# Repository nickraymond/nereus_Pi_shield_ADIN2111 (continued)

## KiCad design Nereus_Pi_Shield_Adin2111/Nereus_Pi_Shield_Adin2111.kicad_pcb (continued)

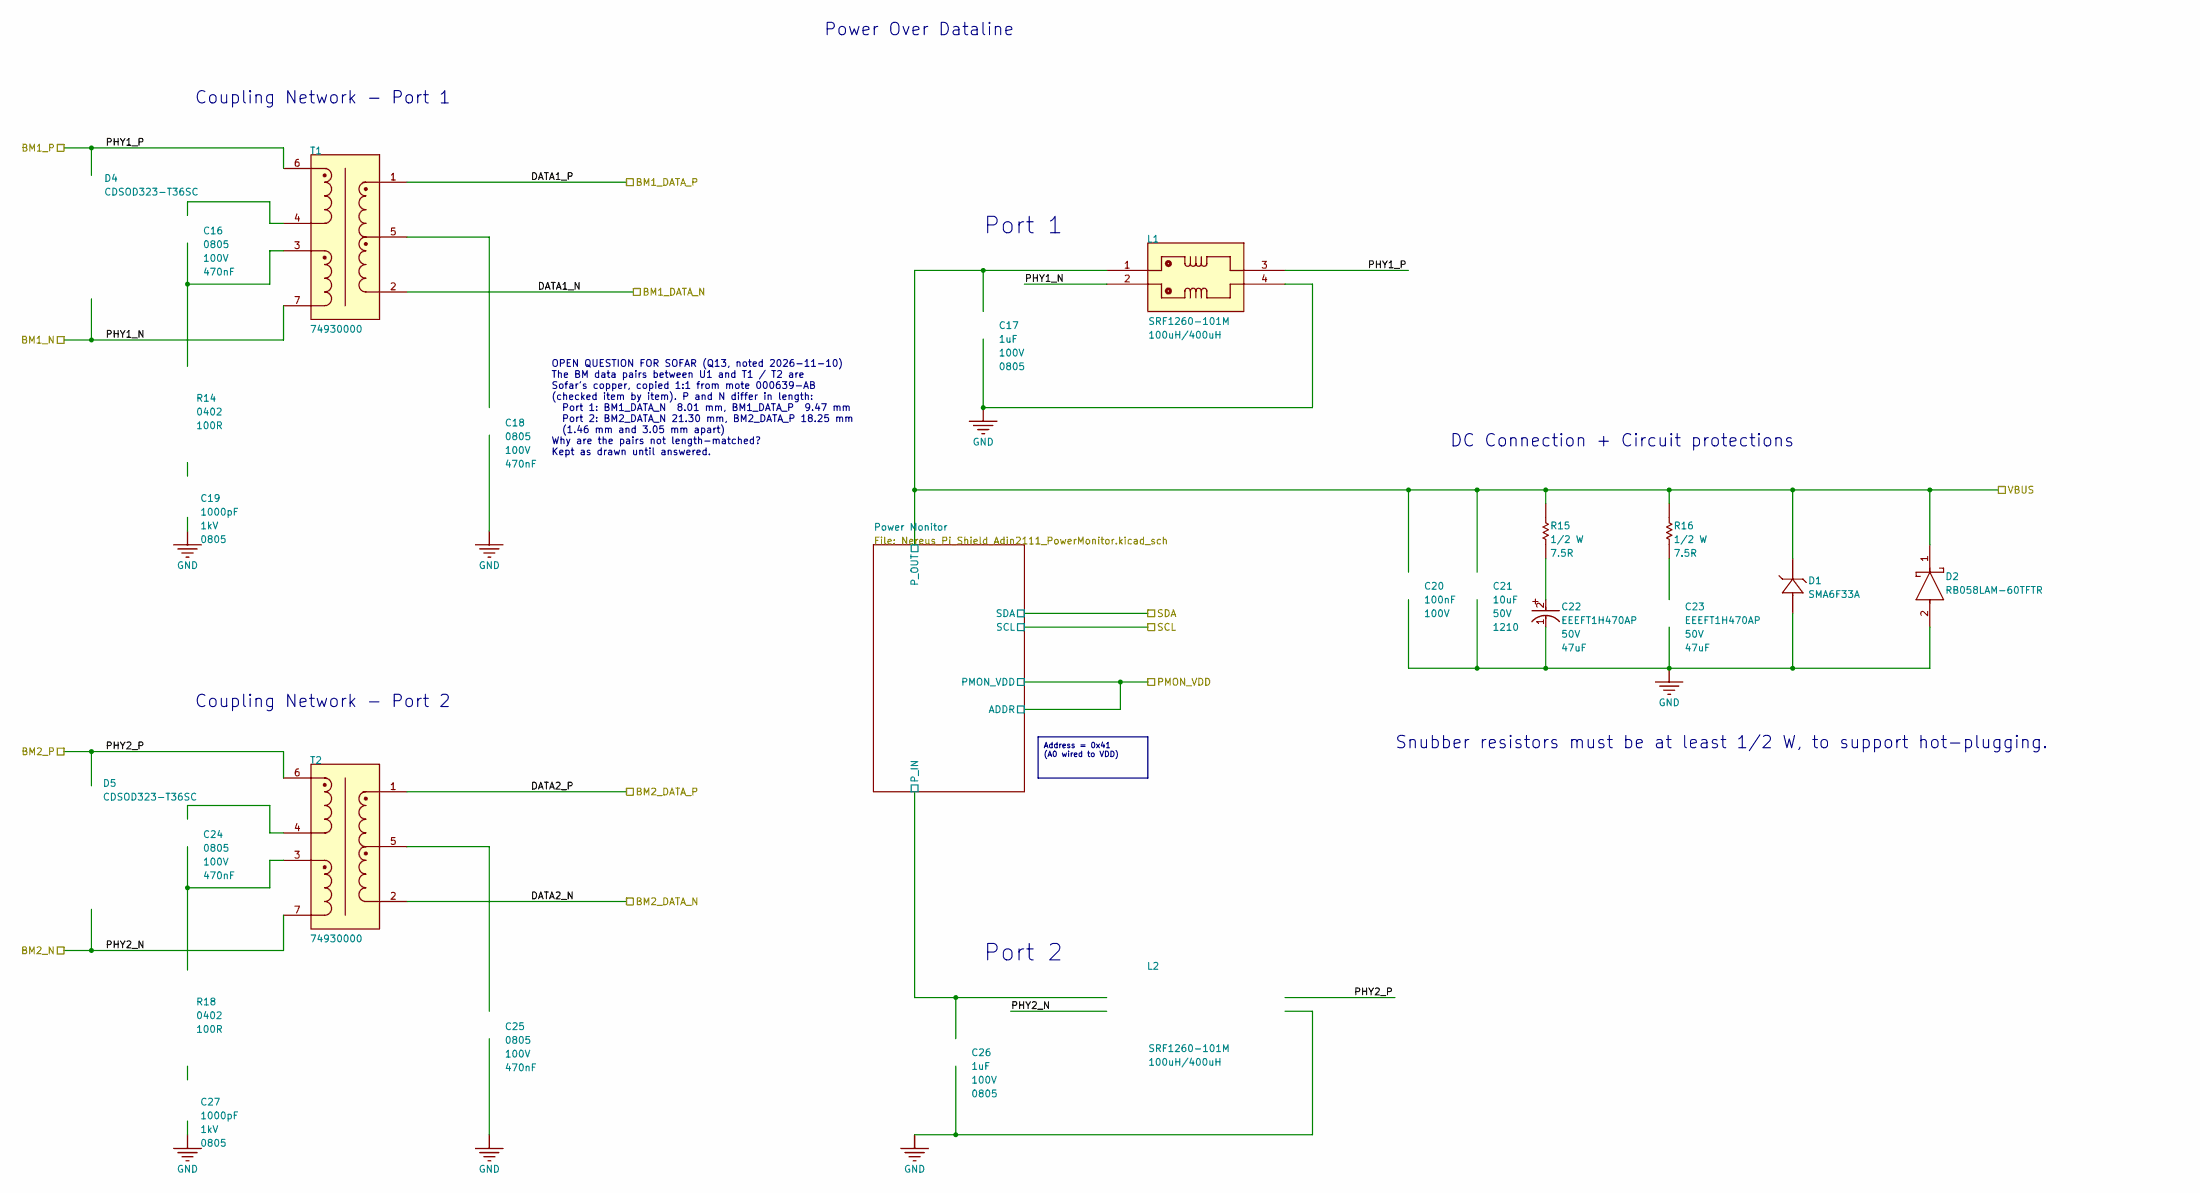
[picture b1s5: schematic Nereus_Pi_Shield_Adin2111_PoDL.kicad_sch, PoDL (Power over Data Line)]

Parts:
C16, C18, C24, C25: 08051C474KAT2A; FP-0805-L_2_01_0_2-W_1_25-MFG; TOLERANCE 10%; VOLTAGE RATING 100V
C17, C26: C2012X7S2A105K125AB; FP-C2012-125-0_2-MFG; VOLTAGE RATING (DC) 100V; VOLTAGE 100V
C19, C27: C0805C102MDRACTU; CAPC2013X145X50LL20T25; VOLTAGE 1kV; PART NUMBER C0805C102MDRACTU
C20: GRM188R72A104KA35D; FP-GRM188-0_1-e0_2_0_5-IPC_B; VOLTAGE RATING (DC) 100V; VOLTAGE 100V
C21: CL32B106KBJNNNE; FP-CL32-IPC_C; VOLTAGE RATING (DC) 50V; VOLTAGE RATING 50V
C22, C23: EEEFT1H470AP; FP-FTD-MFG; VOLTAGE 50V; TOLERANCE 20%
D1: SMA6F33A; SMA6F33A-Footprint-1; VOLTAGE - CLAMPING (MAX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 53.1V; VOLTAGE - REVERSE STAND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 33V; MANUFACTURERPARTNUMBER1 SMA6F33A-M3/H
D2: RB058LAM-60TFTR; FP-PMDTM-MFG
D4, D5: CDSOD323-T36SC; FP-SOD-323-MFG; BREAKDOWN VOLTAGE 40V; CLAMPING VOLTAGE 75V; MANUFACTURER PART NUMBER CDSOD323-T36SC; DIGIKEY DESCRIPTION TVS DIODE 36V 75V SOD323
L1, L2: SRF1260-101M; SRF1260-101M-Footprint-1
R14, R18: RR0510P-101-D; FP-RR0510-IPC_B; RESISTANCE TOLERANCE 0.5%; POWER RATING 63mW
R15, R16: CRCW08057R50FKEAHP; CRCW08057R50FKEAHP-Footprint-1; MANUFACTURERPARTNUMBER CRCW08057R50FKEAHP
T1, T2: 74930000; FP-74930000-MFG

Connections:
/Top-Level Schematic/BM1_DATA_N: T1.2; also elsewhere on the board
/Top-Level Schematic/BM1_DATA_P: T1.1; also elsewhere on the board
/Top-Level Schematic/BM1_N: D4.2, L1.2, T1.7; also elsewhere on the board
/Top-Level Schematic/BM1_P: D4.1, L1.3, T1.6; also elsewhere on the board
/Top-Level Schematic/BM2_DATA_N: T2.2; also elsewhere on the board
/Top-Level Schematic/BM2_DATA_P: T2.1; also elsewhere on the board
/Top-Level Schematic/BM2_N: D5.2, L2.2, T2.7; also elsewhere on the board
/Top-Level Schematic/BM2_P: D5.1, L2.3, T2.6; also elsewhere on the board
/Top-Level Schematic/PoDL/Power Monitor/P_IN: C26.1, L2.1; also elsewhere on the board
GND: C17.2, C18.1, C19.1, C20.2, C21.2, C22.1 (C), C23.1 (C), C25.1, C26.2, C27.1, D1.1 (ANODE), D2.2 (A), L1.4, L2.4; also elsewhere on the board
unnamed: C16.1, R14.1, T1.3
unnamed: C16.2, T1.4
unnamed: C18.2, T1.5
unnamed: C19.2, R14.2
unnamed: C22.2 (A), R15.1
unnamed: C23.2 (A), R16.1
unnamed: C24.1, R18.1, T2.3
unnamed: C24.2, T2.4
unnamed: C25.2, T2.5
unnamed: C27.2, R18.2
VBUS: C17.1, C20.1, C21.1, D1.2 (CATHODE), D2.1 (C), L1.1, R15.2, R16.2; also elsewhere on the board

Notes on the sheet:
OPEN QUESTION FOR SOFAR (Q13, noted 2026-11-10) The BM data pairs between U1 and T1 / T2 are Sofar's copper, copied 1:1 from mote 000639-AB (checked item by item). P and N differ in length: Port 1: BM1_DATA_N 8.01 mm, BM1_DATA_P 9.47 mm Port 2: BM2_DATA_N 21.30 mm, BM2_DATA_P 18.25 mm (1.46 mm and 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
Coupling Network - Port 2
DC Connection + Circuit protections
Snubber resistors must be at least 1/2 W, to support hot-plugging.
Port 2
Coupling Network - Port 1
Port 1
Address = 0x41 (A0 wired to VDD)
Power Over Dataline

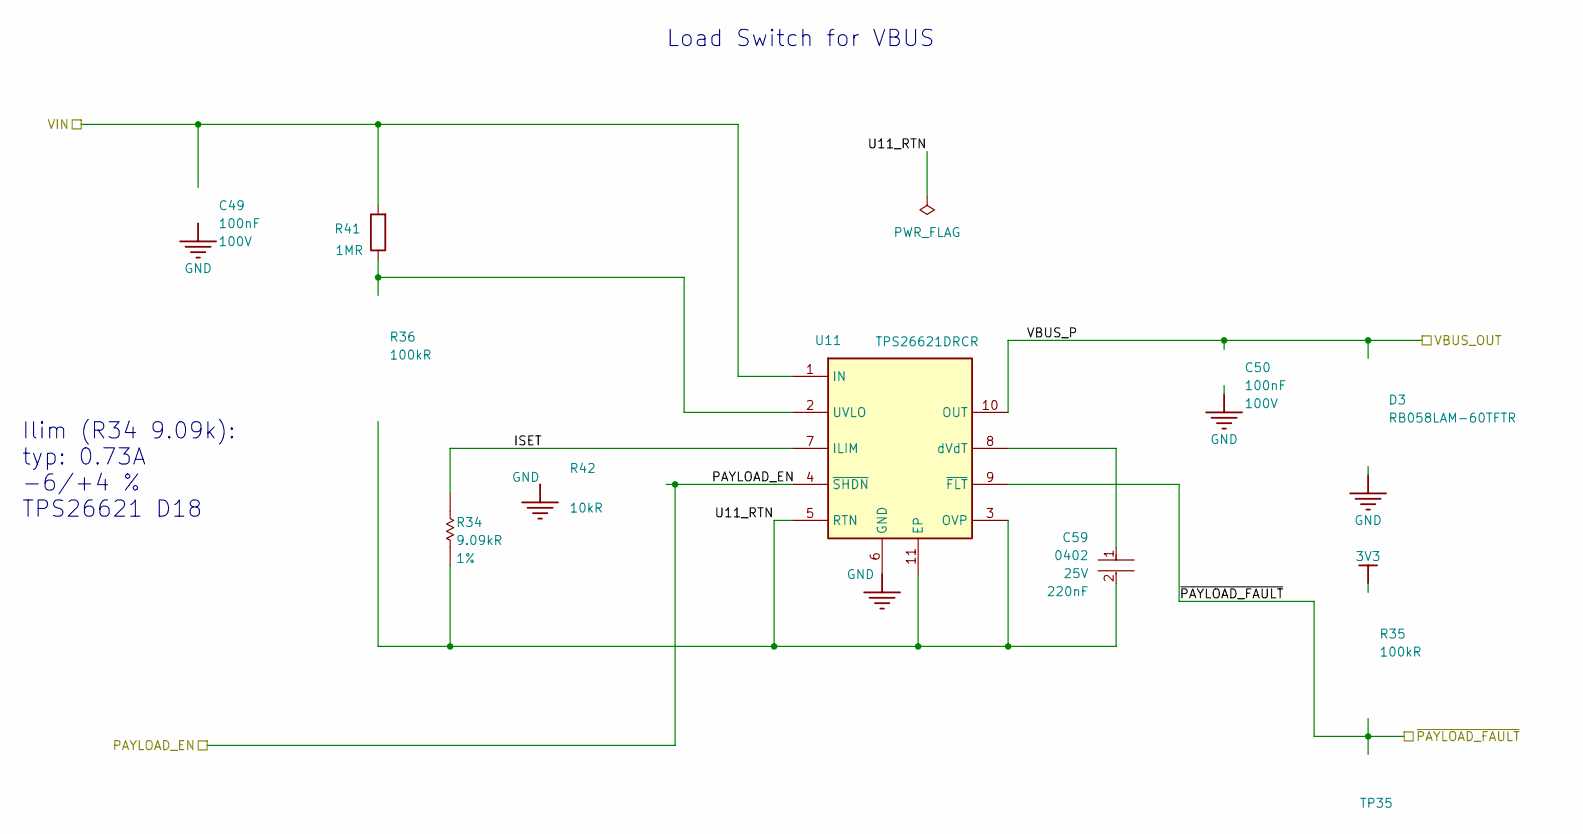
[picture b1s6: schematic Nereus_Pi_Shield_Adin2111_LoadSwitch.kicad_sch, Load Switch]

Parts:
C49, C50: GRM188R72A104KA35D; FP-GRM188-0_1-e0_2_0_5-IPC_B; VOLTAGE RATING (DC) 100V; VOLTAGE 100V
C59: CL05A224KA5NNNC; FP-CL278-IPC_C; VOLTAGE 25V; VOLTAGE RATING 25V
D3: RB058LAM-60TFTR; FP-PMDTM-MFG
R34: RC0402FR-079K09L; FP-RC0402-0_4-IPC_C; TOLERANCE 1%; PART NUMBER RC0402FR-079K09L
R35, R36: RMCF0402FT100K; FP-RMCF0402-IPC_C; TOLERANCE 1%; POWER RATING 62.5mW
R41: RC0402FR-071ML; R_0402_1005Metric; PART NUMBER RC0402FR-071ML
R42: RMCF0402FT10K0; FP-RMCF0402-IPC_C; TOLERANCE 1%; POWER RATING 62.5mW
TP35: TEST_POINT; PCB_TP_1.5mm; PARTTYPE non BOM
U11: TPS26621DRCR; Texas_DRC0010J; LCSC C1848341

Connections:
3V3: R35.2; also elsewhere on the board
/Top-Level Schematic/Load Switch/ISET: R34.2, U11.7 (ILIM)
/Top-Level Schematic/Load Switch/U11_RTN: C59.2, R34.1, R36.1, U11.3 (OVP), U11.5 (RTN), U11.11 (EP)
/Top-Level Schematic/PAYLOAD_EN: R42.1, U11.4 (~SHDN); also elsewhere on the board
/Top-Level Schematic/~PAYLOAD_FAULT: R35.1, TP35.1 (1_1), U11.9 (~FLT); also elsewhere on the board
GND: C49.2, C50.2, D3.2 (A), R42.2, U11.6 (GND); also elsewhere on the board
unnamed: R36.2, R41.1, U11.2 (UVLO)
unnamed: C59.1, U11.8 (dVdT)
VBUS: C49.1, R41.2, U11.1 (IN); also elsewhere on the board
VBUS_OUT: C50.1, D3.1 (C), U11.10 (OUT); also elsewhere on the board

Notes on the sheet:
Load Switch for VBUS
Ilim (R34 9.09k): typ: 0.73A -6/+4 % TPS26621 D18

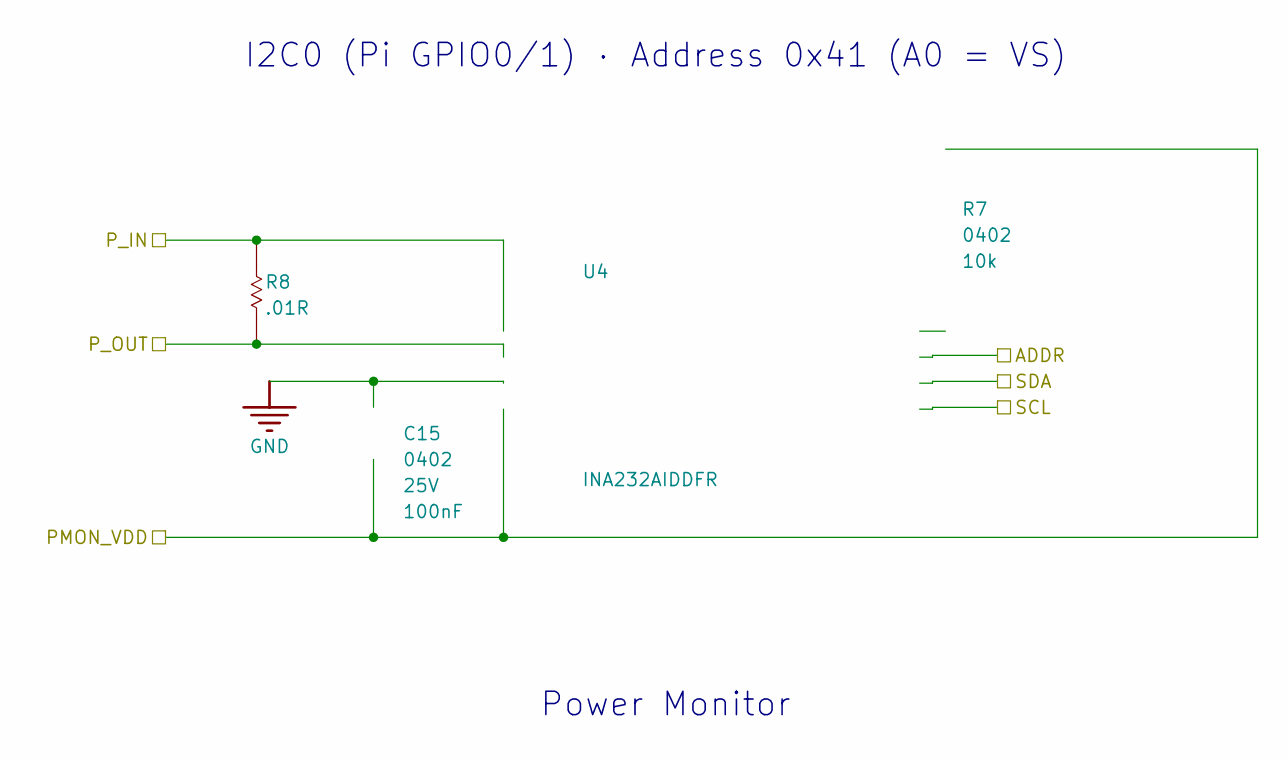
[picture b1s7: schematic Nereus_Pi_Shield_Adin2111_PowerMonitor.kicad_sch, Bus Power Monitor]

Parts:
C15: CL05A104KA5NNNC; FP-CL278-IPC_C; VOLTAGE 25V; VOLTAGE RATING 25V
R7: RC0402JR-0710KL; FP-RC0402-0_4-IPC_C; RESISTANCE TOLERANCE 5%; POWER RATING 62.5mW
R8: UR73D1JTTD10L0F; RESC1608X60X55ML20T10; MANUFACTURERPARTNUMBER UR73D1JTTD10L0F
U4: INA232AIDDFR; INA232AIDDFR-Footprint-1

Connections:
3V3: C15.2, R7.1, U4.4 (VS), U4.7 (A0); also elsewhere on the board
/Top-Level Schematic/I2C0_SCL: U4.5 (SCL); also elsewhere on the board
/Top-Level Schematic/I2C0_SDA: U4.6 (SDA); also elsewhere on the board
/Top-Level Schematic/PoDL/Power Monitor/P_IN: R8.2, U4.1 (IN+); also elsewhere on the board
GND: C15.1, U4.3 (GND); also elsewhere on the board
unnamed: R7.2, U4.8 (ALERT)
VBUS: R8.1, U4.2 (IN-); also elsewhere on the board

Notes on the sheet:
I2C0 (Pi GPIO0/1) · Address 0x41 (A0 = VS)
Power Monitor

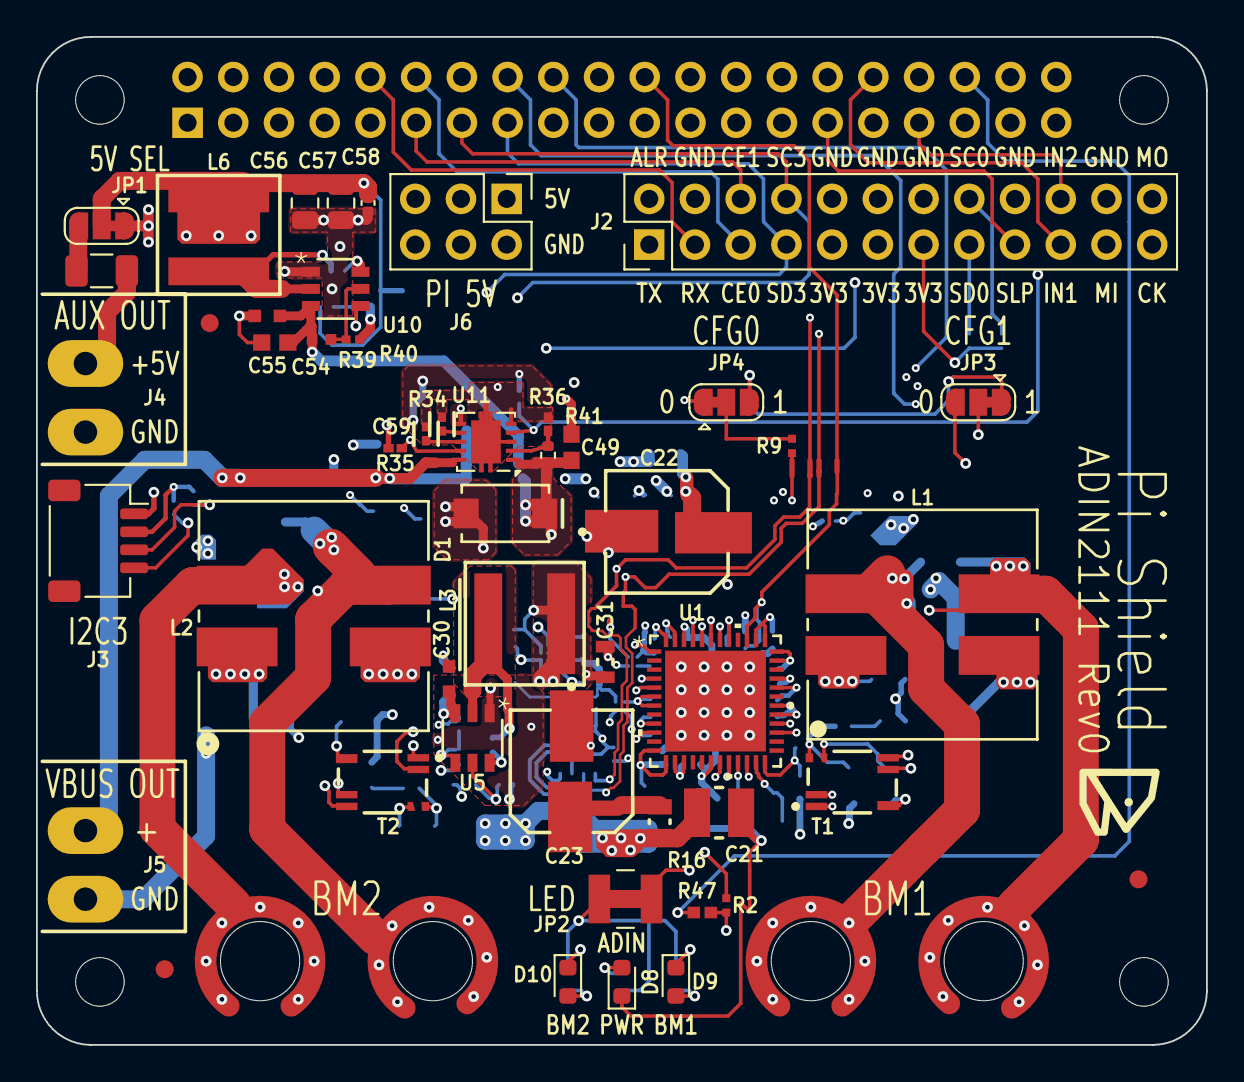
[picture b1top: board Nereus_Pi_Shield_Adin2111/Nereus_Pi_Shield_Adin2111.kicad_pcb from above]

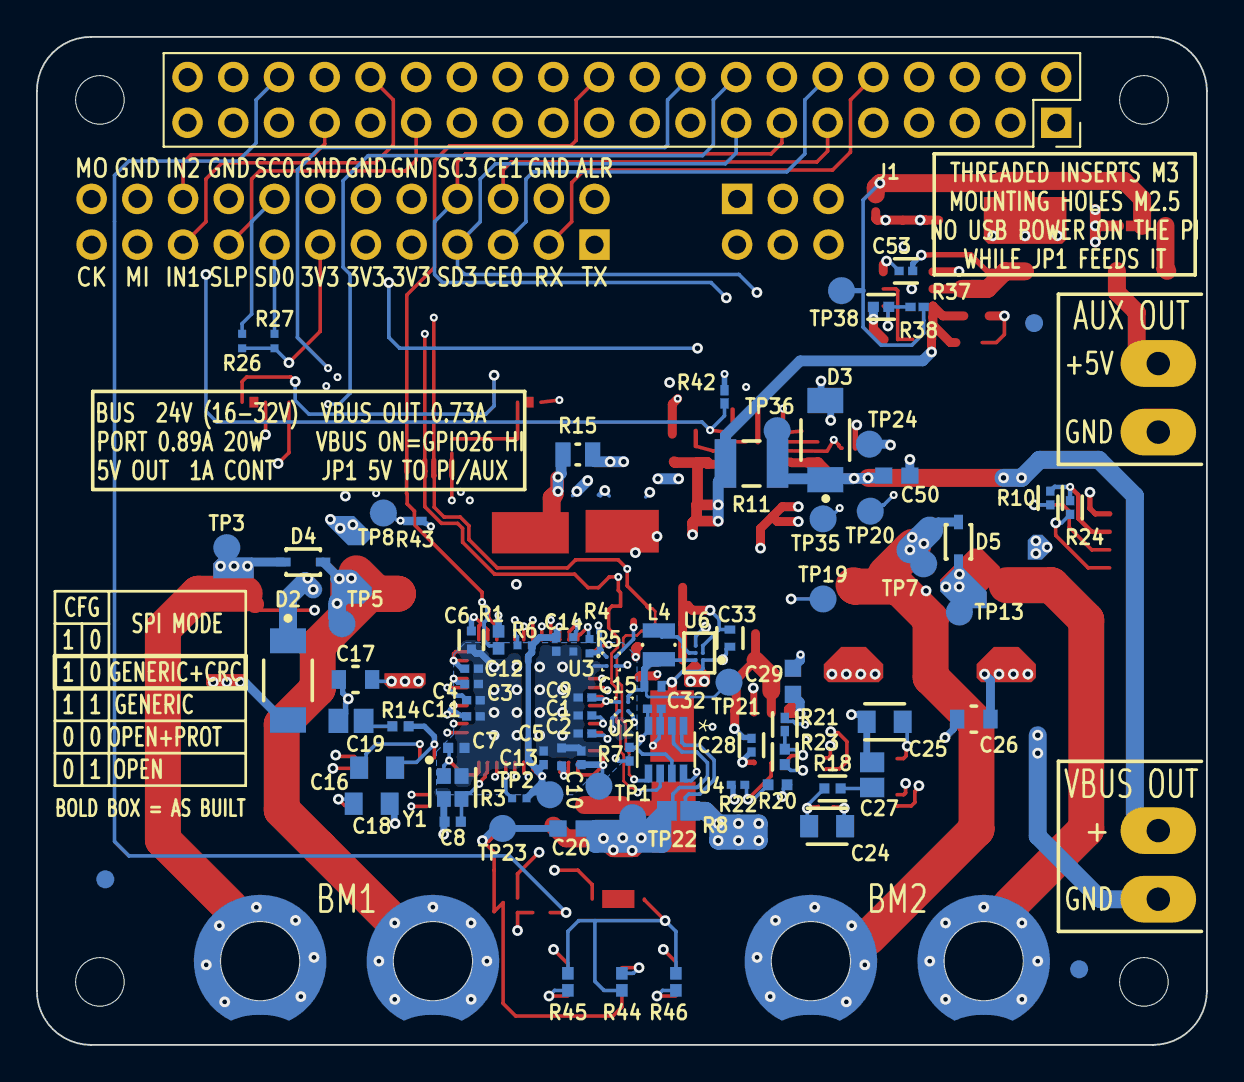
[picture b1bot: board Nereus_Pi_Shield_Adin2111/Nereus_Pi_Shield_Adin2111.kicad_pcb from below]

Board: 6 copper layers, 65.0 x 56.0 mm, 143 parts (90 on the bottom side), 90 nets.

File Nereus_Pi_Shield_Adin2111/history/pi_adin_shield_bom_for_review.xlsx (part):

Sourcing | Refs | Qty | Value (MPN) | Mfr | Planned MPN | Planned Mfr | Planned LCSC | Planned note | DNP | Alt1 MPN | Alt1 Mfr | Alt1 LCSC | Alt2 MPN | Alt2 Mfr | Alt2 LCSC | Alt note | Footprint | Column 1 | Column 2 | Column 3 | Column 4 | Column 5 | Column 6 | Column 7 | Column 8
Not ordered (JLC stock) | C1,C3,C9,C10,C11,C12,C13,C14,C15,C28,C53 | 11.0 | CL05A104KA5NNNC | Samsung | CL05A104KA5NNNC | Samsung | C100072 | As specified; in LCSC stock (checked 2026-10-06) |  |  |  |  |  |  |  |  | Vault:FP-CL278-IPC_C
Not ordered (JLC stock) | C2,C4 | 2.0 | CL05A105KP5NNNC | Samsung | CL05A105KP5NNNC | Samsung | C14445 | As specified; in LCSC stock (checked 2026-10-06) |  |  |  |  |  |  |  |  | Vault:FP-CL511-IPC_C
Not ordered (JLC stock) | C5,C6 | 2.0 | CC0402KRX5R6BB684 | YAGEO | CC0402KRX5R6BB684 | Yageo | C113784 | As specified; in LCSC stock (checked 2026-10-06) |  |  |  |  |  |  |  |  | Vault:FP-CC0402-MFG
Not ordered (JLC stock) | C7,C8 | 2.0 | CC0402JRNPO9BN150 | Yageo | CC0402JRNPO9BN150 | Yageo | C106997 | As specified; in LCSC stock (checked 2026-10-06) |  |  |  |  |  |  |  |  | Vault:FP-CC0402-0_55-IPC_B
Sofar to review / approve alternative | C16,C18,C24,C25 | 4.0 | 08051C474KAT2A | KYOCERA AVX | CC0805KKX7R0BB474 | YAGEO | C596323 | Same spec, 470 nF ±10 % 100 V X7R 0805, largest LCSC stock (250,730 vs the AVX 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 |  | CC0805KKX7R0BB474 | YAGEO | C596323 | 08051C474K4Z2A | KYOCERA AVX | C597303 | 470 nF ±10 % 100 V X7R 0805; PoDL front end: Sofar review | Vault:FP-0805-L_2_01_0_2-W_1_25-MFG
Sofar to review / approve alternative | C17,C26 | 2.0 | C2012X7S2A105K125AB | TDK | C2012X7S2A105KT000N | TDK | C342785 | TDK C2012 series, same 1 µF ±10 % 100 V X7S 0805 per LCSC (thickness not confir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 |  | C2012X7S2A105KT000N | TDK | C342785 | GCM21BC72A105KE36L | Murata | C126585 | 1 µF ±10 % 100 V X7S 0805; power path: Sofar review | Vault:FP-C2012-125-0_2-MFG
Sofar to review / approve alternative | C19,C27 | 2.0 | C0805C102MDRACTU | Kemet | C0805C102KDRACTU | KEMET | C2167549 | Same KEMET series, ±10 % instead of ±20 % (tighter); 1 nF 1 kV X7R 0805; specif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 |  | C0805C102KDRACTU | KEMET | C2167549 | 0805B102K102CT | Walsin | C303890 | 1 nF 1 kV X7R 0805, ±10 % (tighter); PoDL front end: Sofar review | Vault:CAPC2013X145X50LL20T25
Not ordered (JLC stock) | C20,C29,C49,C50,C54 | 5.0 | GRM188R72A104KA35D | Murata | GRM188R72A104KA35D | Murata | C77058 | As specified; in LCSC stock (checked 2026-10-06) |  |  |  |  |  |  |  |  | Vault:FP-GRM188-0_1-e0_2_0_5-IPC_B
Sofar to review / approve alternative | C21 | 1.0 | CL32B106KBJNNNE | Samsung | UMK325AB7106KM-T | Taiyo Yuden | C386167 | 10 µF ±10 % 50 V X7R 1210 from Taiyo Yuden, an established MLCC maker, for the 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 |  | 1210B106K500NT | FH | C116808 | UMK325AB7106KM-T | Taiyo Yuden | C386167 | 10 µF ±10 % 50 V X7R 1210; power path: Sofar review | Vault:FP-CL32-IPC_C
Already ordered qty 60 | C22,C23 | 2.0 | EEEFT1H470AP | Panasonic | EEEFT1H470AP | Panasonic | C92059 | As specified; bus damper with R15/R16; LCSC out of stock (global sourced) |  |  |  |  |  |  |  |  | Vault:FP-FTD-MFG
Not ordered (JLC stock) | C30,C55 | 2.0 | UMK107BBJ225KA-T | Taiyo Yuden | UMK107BBJ225KA-T | Taiyo Yuden | C268016 | As specified; in LCSC stock (checked 2026-10-06); Taiyo Yuden now lists it as M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 |  |  |  |  |  |  |  |  | Vault:FP-0603-L_1_6_0_2-W_0_8_0-MFG
Sofar to review / approve alternative | C31 | 1.0 | C1608X5R0J226M080AC | TDK | CL10A226MQ8NRNC | Samsung | C59461 | Same spec, 22 µF ±20 % 6.3 V X5R 0603; specified TDK out of stock at LCSC (and 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 |  | CL10A226MQ8NRNC | Samsung | C59461 | GRM188R60J226MEA0D | Murata | C77042 | 22 µF ±20 % 6.3 V X5R 0603 | Vault:CAPC1608X100X20ML10
Not ordered (JLC stock) | C32 | 1.0 | GRJ155R60J106ME11D | Murata | GRJ155R60J106ME11D | Murata | C469527 | As specified; in LCSC stock (checked 2026-10-06) |  |  |  |  |  |  |  |  | Vault:FP-GRJ155-0_2-MFG
Not ordered (JLC stock) | C33 | 1.0 | GRM155R60J475ME87D | Murata | GRM155R60J475ME87D | Murata | C76996 | As specified; in LCSC stock (checked 2026-10-06) |  |  |  |  |  |  |  |  | Vault:FP-GRM155-0_15-MFG
Not ordered (JLC stock) | C56,C57 | 2.0 | GRM21BR61C226ME44L | Murata | GRM21BR61C226ME44L | Murata | C86817 | As specified; in LCSC stock (checked 2026-10-06) |  |  |  |  |  |  |  |  | Capacitor_SMD:C_0805_2012Metric
Not ordered (JLC stock) | C58 | 1.0 | GRM155R61A475MEAAD | Murata | GRM155R61A475MEAAD | Murata | C335105 | As specified; in LCSC stock (checked 2026-10-06) |  |  |  |  |  |  |  |  | Capacitor_SMD:C_0402_1005Metric
Already ordered qty 27 | D1 | 1.0 | SMA6F33A | STMicroelectronics | SMA6F33A-M3/H | Vishay |  | Vishay second source (ST SMA6F33A obsolete) |  |  |  |  |  |  |  |  | Vault:SMA6F33A-Footprint-1
Already ordered qty 45 | D2,D3 | 2.0 | RB058LAM-60TFTR | ROHM | RB058LAM-60TFTR | ROHM | C3757753 | As specified; JLC part C3757753 |  |  |  |  |  |  |  |  | Vault:FP-PMDTM-MFG
Not ordered (JLC stock) | D4,D5 | 2.0 | CDSOD323-T36SC | Bourns Inc. | CDSOD323-T36SC | Bourns | C911382 | As specified; in LCSC stock (checked 2026-10-06) |  |  |  |  |  |  |  |  | Vault:FP-SOD-323-MFG
Not ordered (JLC stock) | D8 | 1.0 | KT-0603R | Hubei KENTO Elec | KT-0603R | Hubei KENTO | C2286 | As specified; in LCSC stock (checked 2026-10-06) |  |  |  |  |  |  |  |  | LED_SMD:LED_0603_1608Metric
Not ordered (JLC stock) | D9,D10 | 2.0 | KT-0603YG | Hubei KENTO Elec | KT-0603YG | Hubei KENTO | C2289 | As specified; in LCSC stock (checked 2026-10-06) |  |  |  |  |  |  |  |  | LED_SMD:LED_0603_1608Metric
Not ordered (JLC stock) | F1 | 1.0 | BSMD1206-150-16V | BHFUSE | BSMD1206-150-16V | BHFUSE | C883133 | 1.5 A hold / 3 A trip; LiFePO4 charge bridge open (0.57 A) |  |  |  |  |  |  |  |  | Fuse:Fuse_1206_3216Metric
Sofar to review: header part and height (TBD) | J1 | 1.0 | Raspberry_Pi_2_3 |  | TBD |  |  | 2x20 2.54 mm female socket; candidates C2977589, C7499354 (8.5 mm) |  |  |  |  |  |  |  |  | Connector_PinSocket_2.54mm:PinSocket_2x20_P2.54mm_Vertical
Not ordered (JLC stock) | J3 | 1.0 | SM04B-SRSS-TB(LF)(SN) | JST | SM04B-SRSS-TB(LF)(SN) | JST | C160404 | Qwiic (I2C3) connector |  |  |  |  |  |  |  |  | Connector_JST:JST_SH_SM04B-SRSS-TB_1x04-1MP_P1.00mm_Horizontal
Not ordered (JLC stock) | J4 | 1.0 | S2B-PH-K-S(LF)(SN) | JST | S2B-PH-K-S(LF)(SN) | JST | C173752 | 5V out to LiFePO4wered/Pi+ (through-hole, side entry) |  |  |  |  |  |  |  |  | Connector_JST:JST_PH_S2B-PH-K_1x02_P2.00mm_Horizontal
Not ordered (JLC stock) | J5 | 1.0 | SM02B-GHS-TB | JST | SM02B-GHS-TB | JST | C189893 | As specified; in JLC stock |  |  |  |  |  |  |  |  | Connector_JST:JST_GH_SM02B-GHS-TB_1x02-1MP_P1.25mm_Horizontal
Already ordered qty 42 | L1,L2 | 2.0 | SRF1260-101M | Bourns | SRF1260-101M | Bourns | C6496096 | As specified |  |  |  |  |  |  |  |  | Vault:SRF1260-101M-Footprint-1
Already ordered qty 42 | L3,L6 | 2.0 | PA5432.822NLT | Pulse (YAGEO group) | PA5432.822NLT | Pulse (YAGEO group) |  | As specified; no LCSC listing (global sourced) |  |  |  |  |  |  |  |  | Vault:FP-PA5432_472NLT-MFG
Not ordered (JLC stock) | L4 | 1.0 | DFE201612E-2R2M=P2 | Murata | DFE201612E-2R2M=P2 | Murata | C337893 | As specified; in LCSC stock (checked 2026-10-06) |  |  |  |  |  |  |  |  | Vault:FP-DFE201612C-MFG
Already ordered qty 84 | MP1,MP2,MP3,MP4 | 4.0 | 7.861401536E10 | Wurth Elektronik | 7.861401536E10 | Würth Elektronik | C17256375 | As specified; JLC part C17256375 |  |  |  |  |  |  |  |  | Vault:78614015360-Footprint-2
Not ordered (JLC stock) | R1,R44,R45,R46 | 4.0 | RC0402FR-071K5L | Yageo / Phycomp | RC0402FR-071K5L | Yageo | C114759 | As specified; in LCSC stock (checked 2026-10-06) |  |  |  |  |  |  |  |  | Vault:RESC1005X40X25ML05T10
Not ordered (JLC stock) | R2,R3,R4,R5,R6,R9,R26,R27 | 8.0 | ERJ-2RKF4701X | Panasonic | ERJ-2RKF4701X | Panasonic | C400631 | As specified; in LCSC stock (checked 2026-10-06) |  |  |  |  |  |  |  |  | Vault:RESC1005X40X25LL05T05
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
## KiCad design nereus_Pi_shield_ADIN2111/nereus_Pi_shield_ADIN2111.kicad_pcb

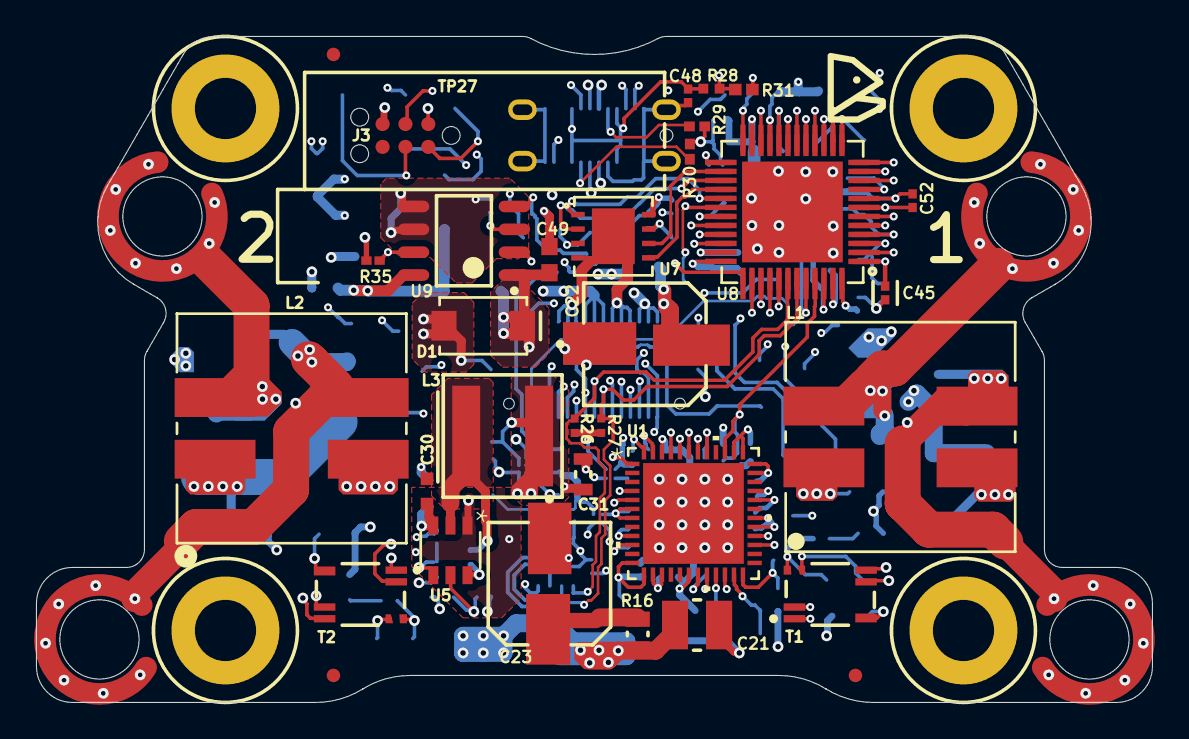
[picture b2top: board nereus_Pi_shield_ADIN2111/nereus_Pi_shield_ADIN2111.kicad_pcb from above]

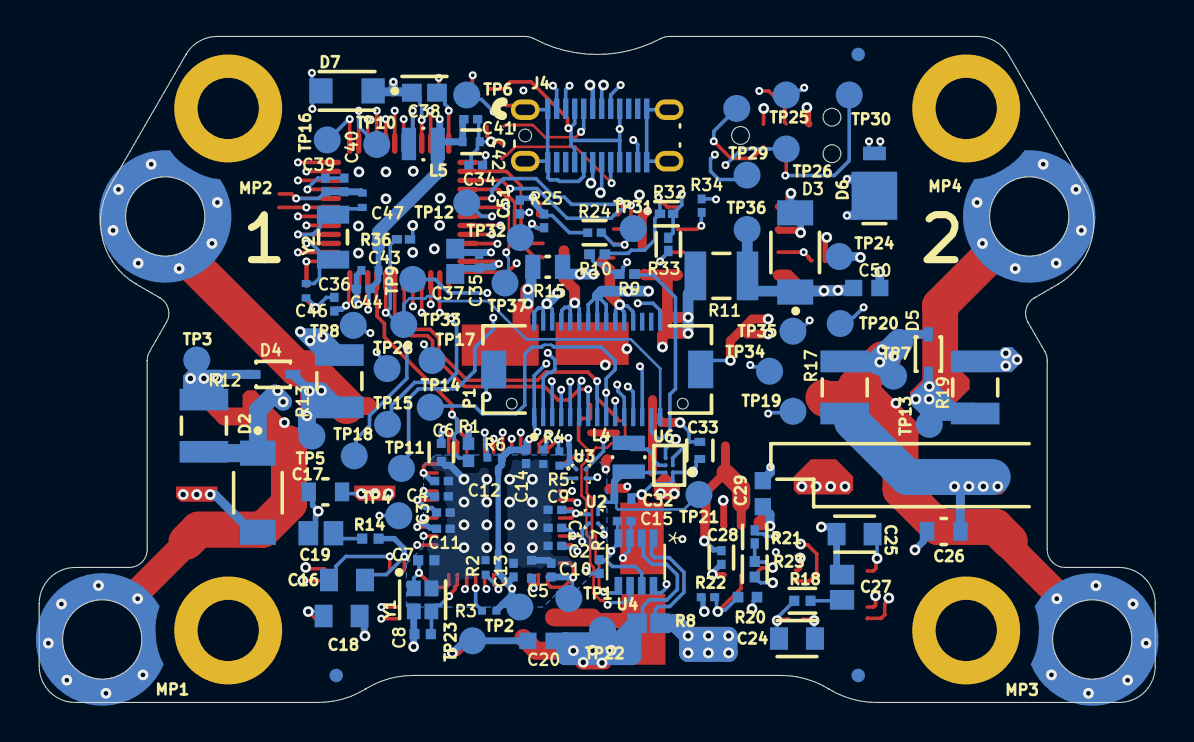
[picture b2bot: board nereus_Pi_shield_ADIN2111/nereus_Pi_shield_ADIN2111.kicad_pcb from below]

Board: 6 copper layers, 62.0 x 37.0 mm, 167 parts (131 on the bottom side), 92 nets.

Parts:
C1, C3, C9, C10, C11, C12, C13, C14, C15, C28, C34, C35, C36, C39, C41, C44, C45, C48, C51, C52: CL05A104KA5NNNC; FP-CL278-IPC_C
C2, C4, C40: CL05A105KP5NNNC; FP-CL511-IPC_C
C5, C6: CC0402KRX5R6BB684; FP-CC0402-MFG
C7, C8: CC0402JRNPO9BN150; FP-CC0402-0_55-IPC_B
C16, C18, C24, C25: 08051C474KAT2A; FP-0805-L_2_01_0_2-W_1_25-MFG
C17, C26: C2012X7S2A105K125AB; FP-C2012-125-0_2-MFG
C19, C27: C0805C102MDRACTU; CAPC2013X145X50LL20T25
C20, C29, C49, C50: GRM188R72A104KA35D; FP-GRM188-0_1-e0_2_0_5-IPC_B
C21: CL32B106KBJNNNE; FP-CL32-IPC_C
C22, C23: EEEFT1H470AP; FP-FTD-MFG
C30: UMK107BBJ225KA-T; FP-0603-L_1_6_0_2-W_0_8_0-MFG
C31: C1608X5R0J226M080AC; CAPC1608X100X20ML10
C32: GRJ155R60J106ME11D; FP-GRJ155-0_2-MFG
C33: GRM155R60J475ME87D; FP-GRM155-0_15-MFG
C37, C38: GRM188D71A106MA73D; FP-GRM188-0_2-IPC_B
C42, C43: LMK105BJ225KV-F; FP-0402-L_1_0_0_05-W_0_5-MFG
C46, C47: CGA2B2C0G1H050C050BA; FP-CGA2B-MFG
D1: SMA6F33A; SMA6F33A-Footprint-1
D2, D3: RB058LAM-60TFTR; FP-PMDTM-MFG
D4, D5: CDSOD323-T36SC; FP-SOD-323-MFG
D6: SS3P3-M3/84A; SS3P3-M3_84A-Footprint-1
D7: SMF3.3; FP-SMF3_3-MFG
FID1, FID2, FID3, FID4, FID5, FID6: FIDUCIAL; FIDUCIAL_075MM
J3: TC2030-FP-sofar; TC2030-FP-Footprint-1
J4: USB4160-03-0070-C; USB4160-03-0070-C-Footprint-1
L1, L2: SRF1260-101M; SRF1260-101M-Footprint-1
L3: PA5432.822NLT; FP-PA5432_472NLT-MFG
L4: DFE201612E-2R2M=P2; FP-DFE201612C-MFG
L5: LQM2MPN2R2NG0L; FP-LQM2MPN_G0-MFG
MP1, MP2, MP3, MP4: 78614015360; 78614015360-Footprint-2
MTG1, MTG2, MTG3, MTG4: Hole_M3
P1: DF17(3.0)-30DS-0.5V(57); FP-DF17_3_0H_-30DS-0_5V_5-MFG
R1, R31: RC0402FR-071K5L; RESC1005X40X25ML05T10
R2, R3, R4, R5, R6, R26, R27: ERJ-2RKF4701X; RESC1005X40X25LL05T05
R7, R24, R25: RC0402JR-0710KL; FP-RC0402-0_4-IPC_C
R8: UR73D1JTTD10L0F; RESC1608X60X55ML20T10
R9, R10: RC0402JR-070RL; RESC1005X40X25NL05T10
R11, R12, R13, R17, R19: CRCW12100000Z0EA; FP-CRCW1210-e3-IPC_B
R14, R18: RR0510P-101-D; FP-RR0510-IPC_B
R15, R16: CRCW08057R50FKEAHP; CRCW08057R50FKEAHP-Footprint-1
R20: CRCW04021M82FKED; FP-CRCW0402-e3-MFG
R21, R32, R33, R35, R36: RMCF0402FT100K; FP-RMCF0402-IPC_C
R22: RC0402FR-07200KL; RESC1005X40X25LL05T10
R23: RC0402FR-0722K1L; FP-RC0402-0_4-IPC_B
R28: ERJ-2RKF1001X; RESC1005X40X25NL05T05
R29, R30: RC0402FR-075K1L; RESC1005X40X25NL05T10
R34: RC0402FR-07374KL; RESC1005X40X25LL05T10
T1, T2: 74930000; FP-74930000-MFG
TP1, TP2, TP3, TP4, TP5, TP6, TP7, TP8, TP9, TP10, TP11, TP12, TP13, TP14, TP15, TP16, TP17, TP18, TP19, TP20, TP21, TP22, TP23, TP24, TP25, TP26, TP27, TP28, TP29, TP30, TP31, TP32, TP33, TP34, TP35, TP36, TP37: TEST_POINT; PCB_TP_1.5mm
U1: ADIN2111BCPZ; ADIN2111BCPZ-Footprint-1
U2, U3: AP22913CN4-7; AP22913CN4-7-Footprint-1
U4: INA232AIDDFR; INA232AIDDFR-Footprint-1
U5: LMR51430YDDCR; SOT-23-THIN-6_DDC_TEX
U6: TPS62840YBGR; FP-YBG0006-MFG
U7: W25Q64JVXGIQ; W25Q64JVXGIQ-Footprint-1
U8: STM32U575CIU6Q; STM32U575CIU6Q-Footprint-2
U9: FPF2700MX; FAIR-SO-8_V
Y1: ABM11W-25.0000MHZ-6-K1Z-T3; FP-ABM11W-MFG
Y2: NX3215SA-32.768K-STD-MUS-2; FP-NX3215SA-MFG

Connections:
1V8: C32.1, L4.2, TP21.1, U2.A2, U6.A2
3V3: C15.2, C31.2, C33.1, C34.1, C35.1, C36.1, C37.1, C38.1, C39.1, C40.1, C45.1, C51.2, D6.1, D7.1, J3.1, J4.A8, L3.2, P1.2, P1.4, P1.6, R7.1, R21.1, R24.1, R25.1, R26.2, R27.2, R32.2, R33.2, R35.2, TP20.1, U3.A2, U4.4, U4.7, U6.B1, U6.C1, U7.8, U8.1, U8.9, U8.21, U8.25, U8.36, U8.48
3V3_Buck_SW: C28.1, L3.1, U5.2
3V3_FB: R21.2, R23.1, U5.4
3V3_UVLO: R20.1, R22.2, U5.5
5VUSB: C48.1, J4.A4, J4.A9, J4.B4, J4.B9, R28.2, TP25.1
ADC1_IN16: R9.2, R10.2, TP19.1, U8.19
ADIN_AVDD: C9.1, C10.1, C11.1, C12.1, TP1.1, U1.6, U1.7, U1.12, U1.13, U1.29, U1.30, U1.35, U1.36, U2.A1
ADIN_CLK25_REF: U1.1, U1.22
ADIN_INT: R1.1, U1.39, U8.45
ADIN_MISO: U1.43, U8.40
ADIN_MOSI: U1.42, U8.41
ADIN_NSS: U1.45, U8.38
ADIN_PWR: TP8.1, U2.B2, U3.B2, U8.6
ADIN_RST: U1.20, U8.10
ADIN_SCK: U1.44, U8.39
ADIN_VDDIO: C13.1, C14.1, R1.2, R3.2, R5.2, R6.2, TP2.1, U1.18, U1.46, U3.A1
BM1_DATA_N: T1.2, U1.27
BM1_DATA_P: T1.1, U1.28
BM1_N: D4.2, L1.2, R13.2, T1.7, TP5.1
BM1_P: D4.1, L1.3, R12.1, T1.6, TP3.1
BM2_DATA_N: T2.2, U1.4
BM2_DATA_P: T2.1, U1.5
BM2_N: D5.2, L2.2, R19.2, T2.7, TP13.1
BM2_P: D5.1, L2.3, R17.1, T2.6, TP7.1
BM_CS: P1.7, TP10.1, U8.14
BM_INT: P1.9, TP11.1, U8.18
BM_MISO: P1.1, TP4.1, U8.16
BM_MOSI-TX3: P1.3, TP6.1, U8.17
BM_SCK-RX3: P1.5, TP9.1, U8.15
BOOT: P1.29, R36.2, TP33.1, U8.44
DVDD1_1P1: C6.1, U1.37, U1.38
DVDD2_1P1: C5.1, U1.14, U1.15
FLASH_CS: U7.1, U8.29
FLASH_MISO: U7.2, U8.27
FLASH_MOSI: U7.5, U8.28
FLASH_SCK: U7.6, U8.26
GND: C1.2, C2.2, C3.2, C4.2, C5.2, C6.2, C7.2, C8.2, C9.2, C10.2, C11.2, C12.2, C13.2, C14.2, C15.1, C17.2, C18.1, C19.1, C20.2, C21.2, C22.1, C23.1, C25.1, C26.2, C27.1, C29.2, C30.2, C31.1, C32.2, C33.2, C34.2, C35.2, C36.2, C37.2, C38.2, C39.2, C40.2, C41.2, C42.2, C43.2, C44.2, C45.2, C46.2, C47.2, C48.2, C49.2, C50.2, C51.1, C52.2, D1.1, D2.2, D3.2, D6.2, D7.2, J3.5, J4.A1, J4.A12, J4.B1, J4.B8, J4.B12, J4.Shell, L1.4, L2.4, P1.8, P1.10, P1.12, P1.20, P1.22, P1.24, P1.31, P1.32, R2.2, R4.2, R13.1, R19.1, R22.1, R23.2, R29.1, R30.1, R31.1, R34.1, R36.1, TP23.1, TP24.1, U1.49, U2.B1, U3.B1, U4.3, U5.1, U6.A1, U6.C2, U7.4, U7.9, U8.8, U8.22, U8.24, U8.35, U8.47, U8.49, U9.5, U9.6, Y1.2, Y1.4
GPIO1: P1.17, TP14.1, U8.5
GPIO2: P1.19, TP15.1, U8.2
I2C1_SCL: P1.15, R26.1, U4.5, U8.42
I2C1_SDA: P1.13, R27.1, U4.6, U8.43
I2C_MUX_RST: P1.25, TP18.1, U8.11
IOEXP_INT: P1.11, TP12.1, U8.31
ISET: R34.2, U9.3
LPUART1_RX: P1.21, TP16.1, U8.13
LPUART1_TX: P1.23, TP17.1, U8.12
MCU_RESET: C52.1, J3.3, J4.B2, P1.30, TP28.1, U8.7
MZ_ADC_EXTRA: P1.27, R9.1
NetC1_1: C1.1, U1.9
NetC2_1: C2.1, U1.10
NetC3_1: C3.1, U1.32
NetC4_1: C4.1, U1.33
NetC7_1: C7.1, U1.24, Y1.1
NetC8_1: C8.1, U1.23, Y1.3
NetC16_1: C16.1, R14.1, T1.3
NetC16_2: C16.2, T1.4
NetC18_2: C18.2, T1.5
NetC19_2: C19.2, R14.2
NetC22_2: C22.2, R15.1
NetC23_2: C23.2, R16.1
NetC24_1: C24.1, R18.1, T2.3
NetC24_2: C24.2, T2.4
NetC25_2: C25.2, T2.5
NetC27_2: C27.2, R18.2
NetC28_2: C28.2, U5.6
NetL4_1: L4.1, U6.B2
NetR2_1: R2.1, U1.19
NetR3_1: R3.1, U1.21
NetR4_1: R4.1, U1.47
NetR5_1: R5.1, U1.48
NetR6_1: R6.1, U1.41
NetR7_2: R7.2, U4.8
NetR24_2: R24.2, TP31.1, U7.3
NetR25_2: R25.2, TP32.1, U7.7
PC14-OSC32_IN: C46.1, U8.3, Y2.1
PC14-OSC32_OUT: C47.1, U8.4, Y2.2
P_IN: C26.1, L2.1, R8.2, R17.2, U4.1
SWDCLK: J3.4, J4.A3, TP30.1, U8.37
SWDIO: J3.2, J4.A2, TP27.1, U8.34
SW_FLAGB: R35.1, TP35.1, U9.7
SW_ON: R10.1, R32.1, U9.4
SW_PGOOD: R33.1, TP34.1, U9.2
USB_CC1: J4.A5, R29.2
USB_CC2: J4.B5, R30.2
USB_N: J4.A7, J4.B7, TP29.1, U8.32
USB_P: J4.A6, J4.B6, TP26.1, U8.33
VBUS: C17.1, C20.1, C21.1, C29.1, C30.1, C49.1, D1.2, D2.1, L1.1, R8.1, R11.1, R12.2, R15.2, R16.2, R20.2, TP22.1, U4.2, U5.3, U9.1
VBUS_OUT: C50.1, D3.1, P1.14, P1.16, P1.18, R11.2, TP36.1, U9.8
VDD11: C41.1, C42.1, C43.1, C44.1, L5.2, U8.23, U8.46
VLXSMPS: L5.1, U8.20
VUSB_DETECT: R28.1, R31.2, TP37.1, U8.30
